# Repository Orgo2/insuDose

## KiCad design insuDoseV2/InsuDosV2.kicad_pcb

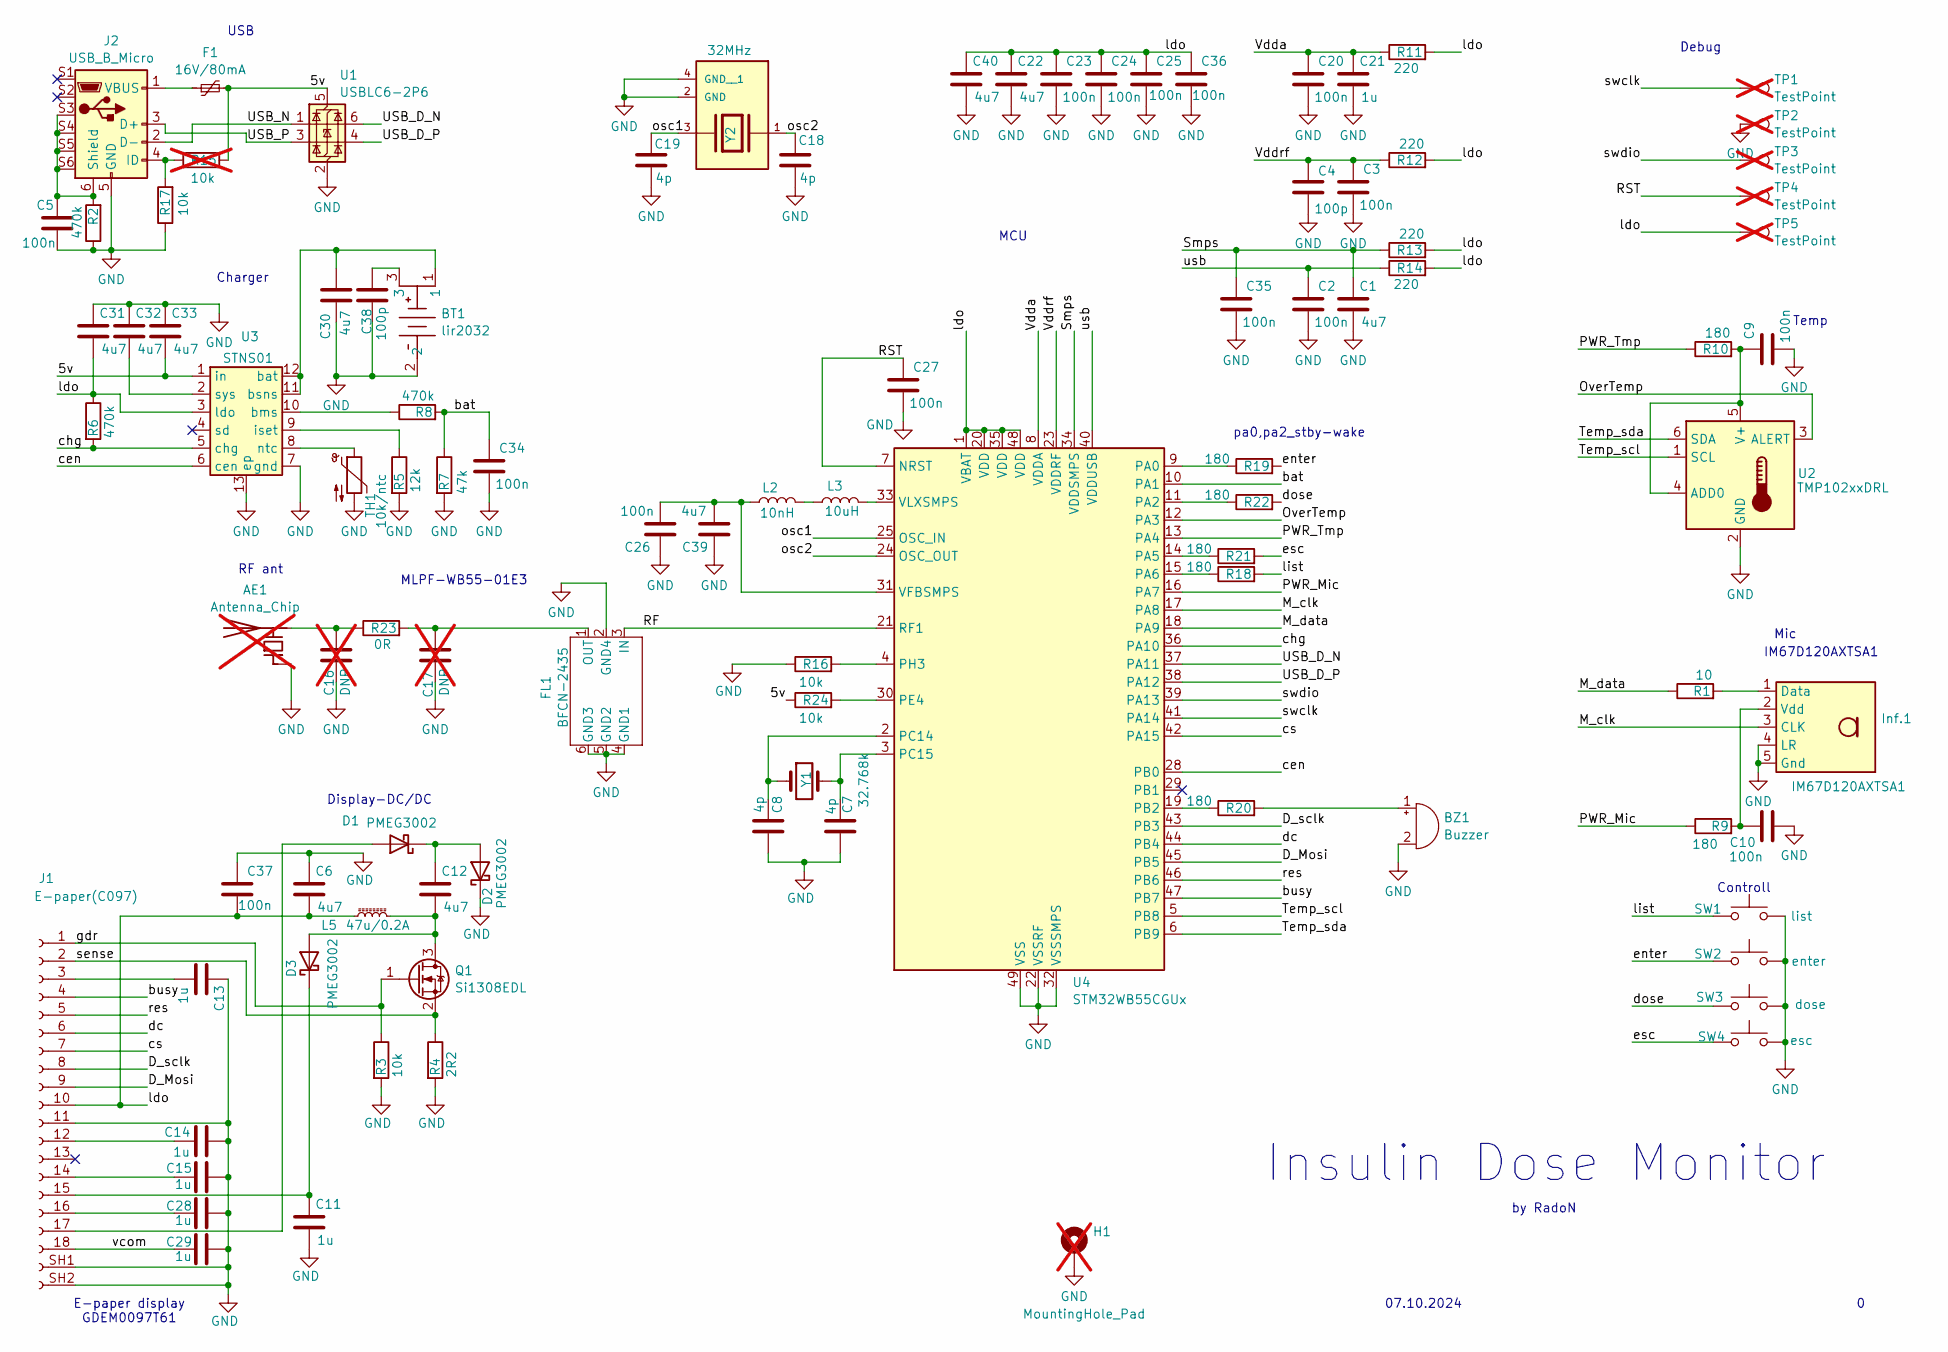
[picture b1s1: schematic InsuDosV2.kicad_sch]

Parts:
AE1: Antenna_Chip; Texas_SWRA117D_2.4GHz_Right; not fitted
BT1: lir2032; BATT_HLDR_via
BZ1: Buzzer; Buzzer_CUI_CPT-9019S-SMT
C1, C6, C12, C22, C30, C31, C32, C33, C39, C40: 4u7; C_0603_1608Metric
C2, C3, C5, C9, C10, C20, C23, C24, C25, C26, C27, C34, C35, C36, C37: 100n; C_0402_1005Metric
C4, C38: 100p; C_0402_1005Metric
C7, C8, C18, C19: 4p; C_0402_1005Metric
C11, C13, C14, C15, C21, C28, C29: 1u; C_0402_1005Metric
C16, C17: DNP; C_0402_1005Metric; not fitted
D1, D2, D3: PMEG3002; D_SOD-882
F1: 16V/80mA; Fuse_0603_1608Metric
FL1: BFCN-2435; St_filter
H1: MountingHole_Pad; MountingHole_2.2mm_M2_ISO14580_Pad_TopBottom; not fitted
Inf.1: IM67D120AXTSA1; Infineon_PG-LLGA-5-2
J1: E-paper(C097); MOLEX_503480-1800
J2: USB_B_Micro; AMPHENOL_10118193-0001LF
L2: 10nH; L_0402_1005Metric
L3: 10uH; L_0603_1608Metric
L5: 47u/0.2A; IND_TAIYO_BRC2016_TAY
Q1: Si1308EDL; SOT-323_SC-70
R1: 10; R_0402_1005Metric
R2, R6, R8: 470k; R_0402_1005Metric
R3, R16, R17, R24: 10k; R_0402_1005Metric
R4: 2R2; R_0402_1005Metric
R5: 12k; R_0402_1005Metric
R7: 47k; R_0402_1005Metric
R9, R10, R18, R19, R20, R21, R22: 180; R_0402_1005Metric
R11, R12, R13, R14: 220; R_0402_1005Metric
R15: 10k; R_0402_1005Metric; not fitted
R23: 0R; R_0402_1005Metric
SW1: list; SW_SPST_B3U-3100P-B
SW2: enter; SW_SPST_B3U-3100P-B
SW3: dose; SW_SPST_B3U-1100P-B
SW4: esc; SW_SPST_B3U-3100P-B
TH1: 10k/ntc; R_0402_1005Metric
TP1, TP2, TP3, TP4, TP5: TestPoint; TestPoint_Pad_1.0x1.0mm; not fitted
U1: USBLC6-2P6; SOT-666
U2: TMP102xxDRL; SOT-563
U3: STNS01; stns01
U4: STM32WB55CGUx; QFN-48-1EP_7x7mm_P0.5mm_EP5.6x5.6mm
Y1: 32.768k; Crystal_SMD_2012-2Pin_2.0x1.2mm
Y2: 32MHz; XTAL_ABM8W-32.0000MHZ-4-B1U-T3; PARTREV 08.09.2018

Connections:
/5v: C33.2, F1.2, R15.2, R24.1, U1.5 (VBUS), U3.1 (in)
/D_Mosi: J1.9, U4.45 (PB5)
/D_sclk: J1.8, U4.43 (PB3)
/M_clk: Inf.1.3 (CLK), U4.17 (PA8)
/M_data: R1.1, U4.18 (PA9)
/OverTemp: U2.3 (ALERT), U4.12 (PA3)
/PWR_Mic: R9.1, U4.16 (PA7)
/PWR_Tmp: R10.1, U4.13 (PA4)
/RF: FL1.3 (IN), U4.21 (RF1)
/RST: C27.1, TP4.1, U4.7 (NRST)
/Smps: C1.1, C35.1, R13.1, U4.34 (VDDSMPS)
/Temp_scl: U2.1 (SCL), U4.5 (PB8)
/Temp_sda: U2.6 (SDA), U4.6 (PB9)
/USB_D_N: U1.6 (I/O1), U4.37 (PA11)
/USB_D_P: U1.4 (I/O2), U4.38 (PA12)
/USB_N: J2.2 (D-), U1.1 (I/O1)
/USB_P: J2.3 (D+), U1.3 (I/O2)
/Vdda: C20.1, C21.1, R11.1, U4.8 (VDDA)
/Vddrf: C3.1, C4.1, R12.1, U4.23 (VDDRF)
/bat: C34.1, R7.1, R8.2, U4.10 (PA1)
/busy: J1.4, U4.47 (PB7)
/cen: U3.6 (cen), U4.28 (PB0)
/chg: R6.2, U3.5 (chg), U4.36 (PA10)
/cs: J1.7, U4.42 (PA15)
/dc: J1.6, U4.44 (PB4)
/dose: R22.2, SW3.2
/enter: R19.2, SW2.1
/esc: R21.2, SW4.2
/gdr: J1.1, Q1.1 (G), R3.1
/ldo: C6.2, C22.1, C23.1, C24.1, C25.1, C31.2, C36.1, C37.2, C40.1, J1.10, L5.1, R6.1, R11.2, R12.2, R13.2, R14.2, TP5.1, U3.3 (ldo), U4.1 (VBAT), U4.20 (VDD), U4.35 (VDD), U4.48 (VDD)
/list: R18.2, SW1.1
/osc1: C19.1, U4.25 (OSC_IN), Y2.3
/osc2: C18.1, U4.24 (OSC_OUT), Y2.1
/res: J1.5, U4.46 (PB6)
/sense: J1.2, Q1.2 (S), R4.1
/swclk: TP1.1, U4.41 (PA14)
/swdio: TP3.1, U4.39 (PA13)
/usb: C2.1, R14.1, U4.40 (VDDUSB)
/vcom: C29.2, J1.18
GND: AE1.2 (FEED), BT1.2, BZ1.2 (-), C1.2, C2.2, C3.2, C4.2, C5.2, C6.1, C7.1, C8.1, C9.2, C10.2, C11.2, C13.1, C14.1, C15.1, C16.2, C17.2, C18.2, C19.2, C20.2, C21.2, C22.2, C23.2, C24.2, C25.2, C26.1, C27.2, C28.1, C29.1, C30.2, C31.1, C32.1, C33.1, C34.2, C35.2, C36.2, C37.1, C38.1, C39.1, C40.2, D2.1 (K), FL1.2 (GND4), FL1.4 (GND1), FL1.5 (GND2), FL1.6 (GND3), H1.1, Inf.1.4 (LR), Inf.1.5 (Gnd), J1.11, J1.SH1, J1.SH2, J2.5 (GND), R2.1, R3.2, R4.2, R5.2, R7.2, R16.1, R17.1, SW1.2, SW1.3, SW2.2, SW2.3, SW3.1, SW3.3, SW4.1, SW4.3, TH1.2, TP2.1, U1.2 (GND), U2.2 (GND), U3.7 (gnd), U3.13 (ep), U4.22 (VSSRF), U4.32 (VSSSMPS), U4.49 (VSS), Y2.2 (GND), Y2.4 (GND__1)
unnamed: AE1.1 (PCB_Trace), C16.1, R23.1
unnamed: BT1.3, C38.2
unnamed: BZ1.1 (+), R20.2
unnamed: D1.2 (A), J1.17
unnamed: C12.1, D1.1 (K), D2.2 (A)
unnamed: C12.2, D3.2 (A), L5.2, Q1.3 (D)
unnamed: C11.1, D3.1 (K), J1.15
unnamed: C17.1, FL1.1 (OUT), R23.2
unnamed: Inf.1.1 (Data), R1.2
unnamed: C10.1, Inf.1.2 (Vdd), R9.2
unnamed: C13.2, J1.3
unnamed: C14.2, J1.12
unnamed: C15.2, J1.14
unnamed: C28.2, J1.16
unnamed: J2.4 (ID), R15.1, R17.2
unnamed: C5.1, J2.6 (Shield), J2.S3, J2.S4, J2.S5, J2.S6, R2.2
unnamed: F1.1, J2.1 (VBUS)
unnamed: L2.2, L3.1
unnamed: R24.2, U4.30 (PE4)
unnamed: C9.1, R10.2, U2.4 (ADD0), U2.5 (V+)
unnamed: BT1.1, C30.1, U3.11 (bsns), U3.12 (bat)
unnamed: R8.1, U3.10 (bms)
unnamed: R5.1, U3.9 (iset)
unnamed: TH1.1, U3.8 (ntc)
unnamed: C32.2, U3.2 (sys)
unnamed: R19.1, U4.9 (PA0)
unnamed: R22.1, U4.11 (PA2)
unnamed: R21.1, U4.14 (PA5)
unnamed: R18.1, U4.15 (PA6)
unnamed: R20.1, U4.19 (PB2)
unnamed: C8.2, U4.2 (PC14), Y1.1
unnamed: C7.2, U4.3 (PC15), Y1.2
unnamed: R16.2, U4.4 (PH3)
unnamed: C26.2, C39.2, L2.1, U4.31 (VFBSMPS)
unnamed: L3.2, U4.33 (VLXSMPS)

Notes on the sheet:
Insulin Dose Monitor
USB
Mic
Temp
pa0,pa2_stby-wake
RF ant
Controll
IM67D120AXTSA1
07.10.2024
Display-DC/DC
E-paper display GDEM0097T61
Debug
Charger
by RadoN
MCU
MLPF-WB55-01E3

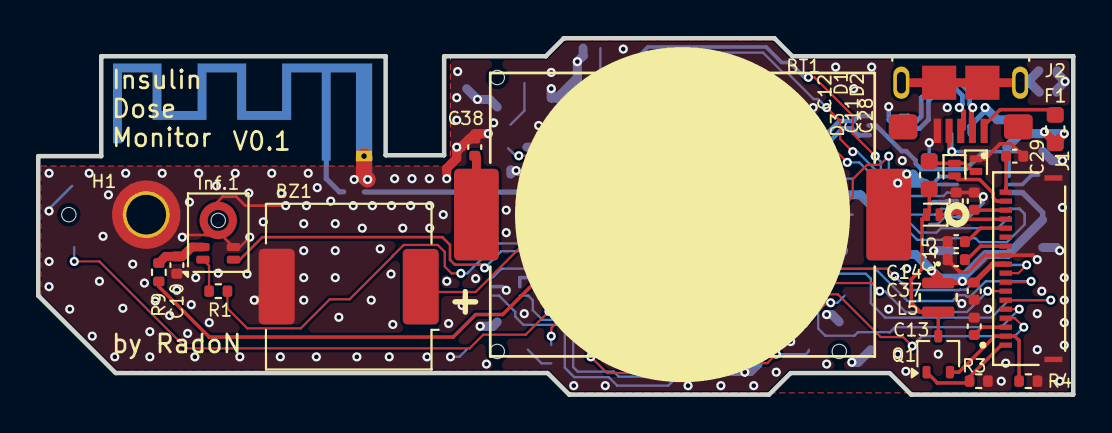
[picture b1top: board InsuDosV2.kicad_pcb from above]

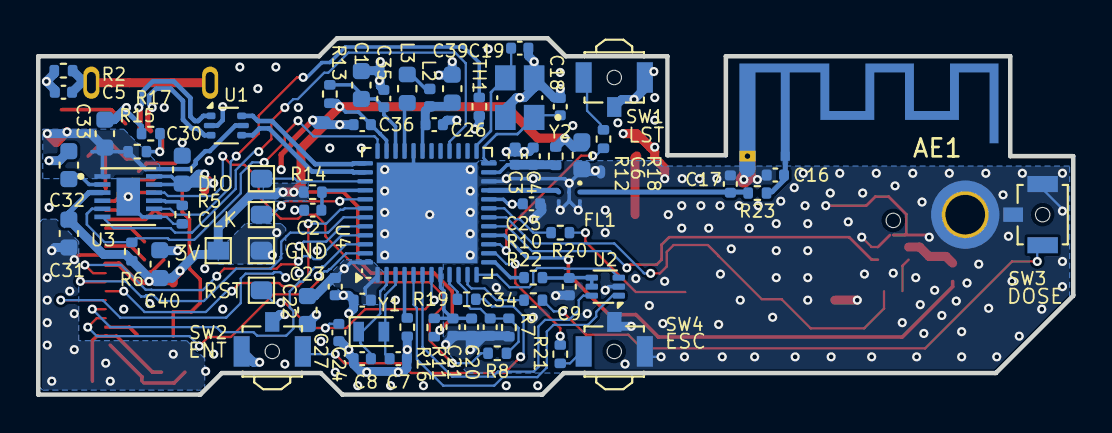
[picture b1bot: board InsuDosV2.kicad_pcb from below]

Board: 4 copper layers, 57.5 x 19.8 mm, 95 parts (69 on the bottom side), 74 nets.

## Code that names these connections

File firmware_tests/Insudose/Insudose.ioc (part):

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Mcu.Name=STM32WB55CGUx
Mcu.Package=UFQFPN48
Mcu.UserName=STM32WB55CGUx
PA0.GPIOParameters=GPIO_PuPd,GPIO_Label,GPIO_ModeDefaultEXTI
PA0.GPIO_Label=ENT
PA0.GPIO_ModeDefaultEXTI=GPIO_MODE_IT_FALLING
PA0.GPIO_PuPd=GPIO_PULLUP
PA0.Signal=GPXTI0
PA1.GPIOParameters=GPIO_Label
PA1.GPIO_Label=BATT
PA1.Signal=ADCx_IN6
PA10.Mode=PDM_Master_Mode_CK1
PA10.Signal=SAI1_D1
PA11.Mode=Device
PA11.Signal=USB_DM
PA12.Mode=Device
PA12.Signal=USB_DP
PA13.Mode=Serial_Wire
PA13.Signal=SYS_JTMS-SWDIO
PA14.Mode=Serial_Wire
PA14.Signal=SYS_JTCK-SWCLK
PA15.GPIOParameters=GPIO_Label
PA15.GPIO_Label=D_CS
PA15.Signal=GPIO_Output
PA2.GPIOParameters=GPIO_PuPd,GPIO_Label,GPIO_ModeDefaultEXTI
PA2.GPIO_Label=DOSE
PA2.GPIO_ModeDefaultEXTI=GPIO_MODE_IT_FALLING
PA2.GPIO_PuPd=GPIO_PULLUP
PA2.Signal=GPXTI2
PA3.Mode=PDM_Master_Mode_CK1
PA3.Signal=SAI1_CK1
PA4.GPIOParameters=GPIO_Label
PA4.GPIO_Label=PW_TMP
PA4.Signal=GPIO_Output
PA5.GPIOParameters=GPIO_PuPd,GPIO_Label
PA5.GPIO_Label=ESC
PA5.GPIO_PuPd=GPIO_PULLUP
PA5.Signal=GPIO_Input
PA6.GPIOParameters=GPIO_PuPd,GPIO_Label
PA6.GPIO_Label=LIST
PA6.GPIO_PuPd=GPIO_PULLUP
PA6.Signal=GPIO_Input
PA7.GPIOParameters=GPIO_Label
PA7.GPIO_Label=PW_MIC
PA7.Signal=GPIO_Output
PA8.Mode=CK2
PA8.Signal=SAI1_CK2
PA9.Mode=3_4_MicroPhones
PA9.Signal=SAI1_D2
PB0.GPIOParameters=GPIO_Label
PB0.GPIO_Label=CEN
PB0.Signal=GPIO_Input
PB2.GPIOParameters=GPIO_Label
PB2.GPIO_Label=BUZZ
PB2.Mode=WaveformGeneration
PB2.Signal=LPTIM1_OUT
PB3.GPIOParameters=GPIO_Label
PB3.GPIO_Label=D_SCLK
PB3.Signal=GPIO_Output
PB4.GPIOParameters=GPIO_Label
PB4.GPIO_Label=D_DC
PB4.Signal=GPIO_Output
PB5.GPIOParameters=GPIO_Label
PB5.GPIO_Label=D_MOSI
PB5.Signal=GPIO_Output
PB6.GPIOParameters=GPIO_Label
PB6.GPIO_Label=D_RST
PB6.Signal=GPIO_Output
PB7.GPIOParameters=GPIO_Label
PB7.GPIO_Label=D_BUSY
PB7.Signal=GPIO_Input
PB8.GPIOParameters=GPIO_Pu
PB8.GPIO_Pu=GPIO_PULLUP
PB8.Mode=I2C
PB8.Signal=I2C1_SCL
PB9.GPIOParameters=GPIO_Pu
PB9.GPIO_Pu=GPIO_PULLUP
PB9.Mode=I2C
PB9.Signal=I2C1_SDA
PC14-OSC32_IN.Mode=LSE-External-Oscillator
PC14-OSC32_IN.Signal=RCC_OSC32_IN
PC15-OSC32_OUT.Mode=LSE-External-Oscillator
PC15-OSC32_OUT.Signal=RCC_OSC32_OUT
PE4.GPIOParameters=GPIO_Label,GPIO_ModeDefaultEXTI
PE4.GPIO_Label=USB_I
PE4.GPIO_ModeDefaultEXTI=GPIO_MODE_IT_RISING
PE4.Signal=GPXTI4
RCC.HSE_VALUE=32000000
RCC.SYSCLKFreq_VALUE=64000000
RCC.SYSCLKSource=RCC_SYSCLKSOURCE_PLLCLK
board=custom

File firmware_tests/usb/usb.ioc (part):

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Mcu.Name=STM32WB55CGUx
Mcu.Package=UFQFPN48
Mcu.UserName=STM32WB55CGUx
PA0.GPIOParameters=GPIO_Label
PA0.GPIO_Label=Enter
PA0.Signal=GPXTI0
PA1.Signal=ADCx_IN6
PA10.GPIOParameters=GPIO_Label
PA10.GPIO_Label=M_d1_chgstate
PA10.Mode=PDM_Master_Mode_CK2
PA10.Signal=SAI1_D1
PA11.Mode=Device
PA11.Signal=USB_DM
PA12.Mode=Device
PA12.Signal=USB_DP
PA13.Mode=Serial_Wire
PA13.Signal=SYS_JTMS-SWDIO
PA14.Mode=Serial_Wire
PA14.Signal=SYS_JTCK-SWCLK
PA15.GPIOParameters=GPIO_Label
PA15.GPIO_Label=D_cs
PA15.Signal=GPIO_Output
PA2.GPIOParameters=GPIO_PuPd,GPIO_Label,GPIO_ModeDefaultEXTI
PA2.GPIO_Label=Dose
PA2.GPIO_ModeDefaultEXTI=GPIO_MODE_IT_RISING_FALLING
PA2.GPIO_PuPd=GPIO_PULLUP
PA2.Signal=GPXTI2
PA3.GPIOParameters=GPIO_PuPd,GPIO_Label,GPIO_ModeDefaultEXTI
PA3.GPIO_Label=Temp_alarm
PA3.GPIO_ModeDefaultEXTI=GPIO_MODE_IT_FALLING
PA3.GPIO_PuPd=GPIO_PULLUP
PA3.Signal=GPXTI3
PA4.GPIOParameters=GPIO_PuPd,GPIO_Label
PA4.GPIO_Label=Temp_PWR
PA4.GPIO_PuPd=GPIO_NOPULL
PA4.Signal=GPIO_Output
PA5.GPIOParameters=GPIO_PuPd,GPIO_Label
PA5.GPIO_Label=Esc
PA5.GPIO_PuPd=GPIO_PULLUP
PA5.Signal=GPIO_Input
PA6.GPIOParameters=GPIO_PuPd,GPIO_Label
PA6.GPIO_Label=List
PA6.GPIO_PuPd=GPIO_PULLUP
PA6.Signal=GPIO_Input
PA7.GPIOParameters=GPIO_Label
PA7.GPIO_Label=M_pwr
PA7.Signal=GPIO_Output
PA8.GPIOParameters=GPIO_Label
PA8.GPIO_Label=M_ck2
PA8.Mode=PDM_Master_Mode_CK2
PA8.Signal=SAI1_CK2
PA9.GPIOParameters=GPIO_Label
PA9.GPIO_Label=M_d2
PA9.Mode=3_4_MicroPhones
PA9.Signal=SAI1_D2
PB0.GPIOParameters=GPIO_Label
PB0.GPIO_Label=CH_cen
PB0.Signal=GPIO_Output
PB2.Mode=WaveformGeneration
PB2.Signal=LPTIM1_OUT
PB3.GPIOParameters=GPIO_Label
PB3.GPIO_Label=D_clk
PB3.Signal=GPIO_Output
PB4.GPIOParameters=GPIO_Label
PB4.GPIO_Label=D_dc
PB4.Signal=GPIO_Output
PB5.GPIOParameters=GPIO_Label
PB5.GPIO_Label=D_mosi
PB5.Signal=GPIO_Output
PB6.GPIOParameters=GPIO_Label
PB6.GPIO_Label=D_rst
PB6.Signal=GPIO_Output
PB7.GPIOParameters=GPIO_Label
PB7.GPIO_Label=D_busy
PB7.Signal=GPXTI7
PB8.GPIOParameters=GPIO_Label,GPIO_Pu
PB8.GPIO_Label=Temp_SDA
PB8.GPIO_Pu=GPIO_PULLUP
PB8.Mode=I2C
PB8.Signal=I2C1_SCL
PB9.GPIOParameters=GPIO_Label,GPIO_Pu
PB9.GPIO_Label=Temp_SDA
PB9.GPIO_Pu=GPIO_PULLUP
PB9.Mode=I2C
PB9.Signal=I2C1_SDA
PC14-OSC32_IN.Mode=LSE-External-Oscillator
PC14-OSC32_IN.Signal=RCC_OSC32_IN
PC15-OSC32_OUT.Mode=LSE-External-Oscillator
PC15-OSC32_OUT.Signal=RCC_OSC32_OUT
PE4.GPIOParameters=GPIO_Label,GPIO_ModeDefaultEXTI
PE4.GPIO_Label=PWR detect
PE4.GPIO_ModeDefaultEXTI=GPIO_MODE_IT_RISING_FALLING
PE4.Signal=GPXTI4
RCC.HSE_VALUE=32000000
RCC.SYSCLKFreq_VALUE=32000000
RCC.SYSCLKSource=RCC_SYSCLKSOURCE_PLLCLK
board=custom

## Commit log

2025-01-18 project updated
2025-01-18 old project deleted
2025-06-19 ulozenie po dlhsom case orgiginal epaper display drivre pridane
2025-07-27 added 5v usb detection
    pcb not finished, drc missing, 3d models missing, project needs to be cleaned up
2025-11-01 astest update
2025-11-01 all messy ackage added
2025-11-01 update insudos, copilot skuska
2025-11-01 updatovanie drivrov pomocou copilota
2025-11-07 uprava kniznic tmp a charger, pridany adcwatchdog na baterku.
2025-11-07 usb descriptor not working but bootloader is, save before gpt update
2025-11-08 tmp102 fixed errors
2025-11-08 uprava warningu v tmp102
2026-03-30 insudose usb update-log ok, tmp ok, rtc ok epd ok mic-in progress
2026-03-30 pdm debug added
2026-03-30 nove hal, pdm uz cosi robi co nakodil chatgpt. idem teraz prerobit pdm na hal verziu....
2026-04-02 nikrofon postaveny na hal uz nieco robi
2026-04-04 mic fixed
2026-04-07 microphonic dose detector in progress, click analysis added
